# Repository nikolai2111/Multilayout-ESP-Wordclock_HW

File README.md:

# Multilayout-ESP-Wordclock_HW
This is the first unofficial hardware (PCB) for the [Multilayout-ESP-Wordclock](https://github.com/ESPWortuhr/Multilayout-ESP-Wordclock). The currently supported layout is a 10x11 with the 4 LEDs in the corner (total 114 LEDs). The dimensions are 240 x 240 mm. In the future, maybe more than one PCBs will be available as branch, but we will see how it goes.

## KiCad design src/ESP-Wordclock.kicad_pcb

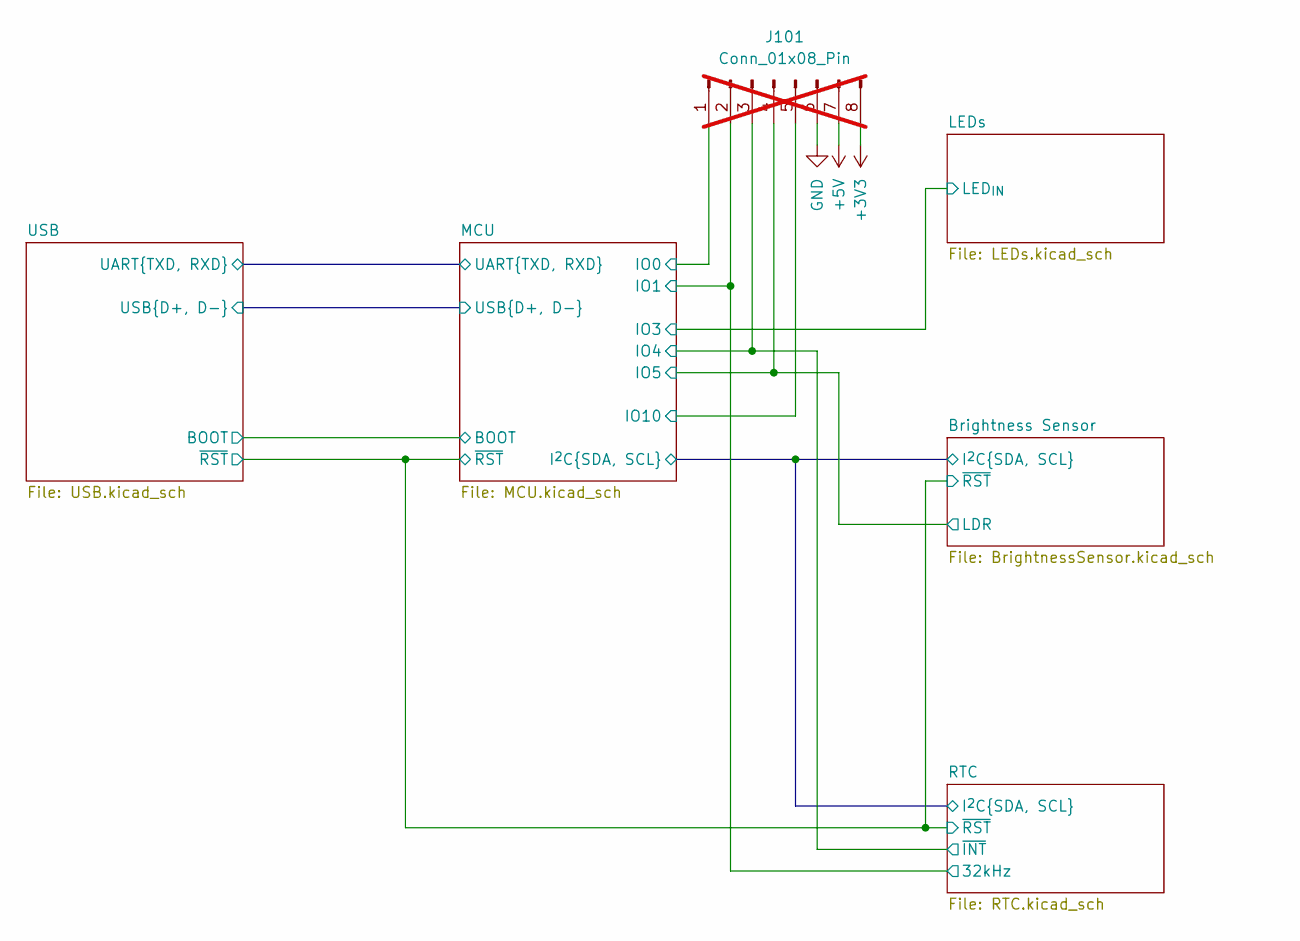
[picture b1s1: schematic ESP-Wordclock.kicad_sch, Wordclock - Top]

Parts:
J101: Conn_01x08_Pin; PinHeader_1x08_P2.54mm_Vertical; not fitted

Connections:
+3V3: J101.8; also elsewhere on the board
+5V: J101.7; also elsewhere on the board
/Brightness Sensor/LDR: J101.4; also elsewhere on the board
/MCU/IO0: J101.1; also elsewhere on the board
/MCU/IO1: J101.2; also elsewhere on the board
/MCU/IO4: J101.3; also elsewhere on the board
/MCU/IO10: J101.5; also elsewhere on the board
GND: J101.6; also elsewhere on the board

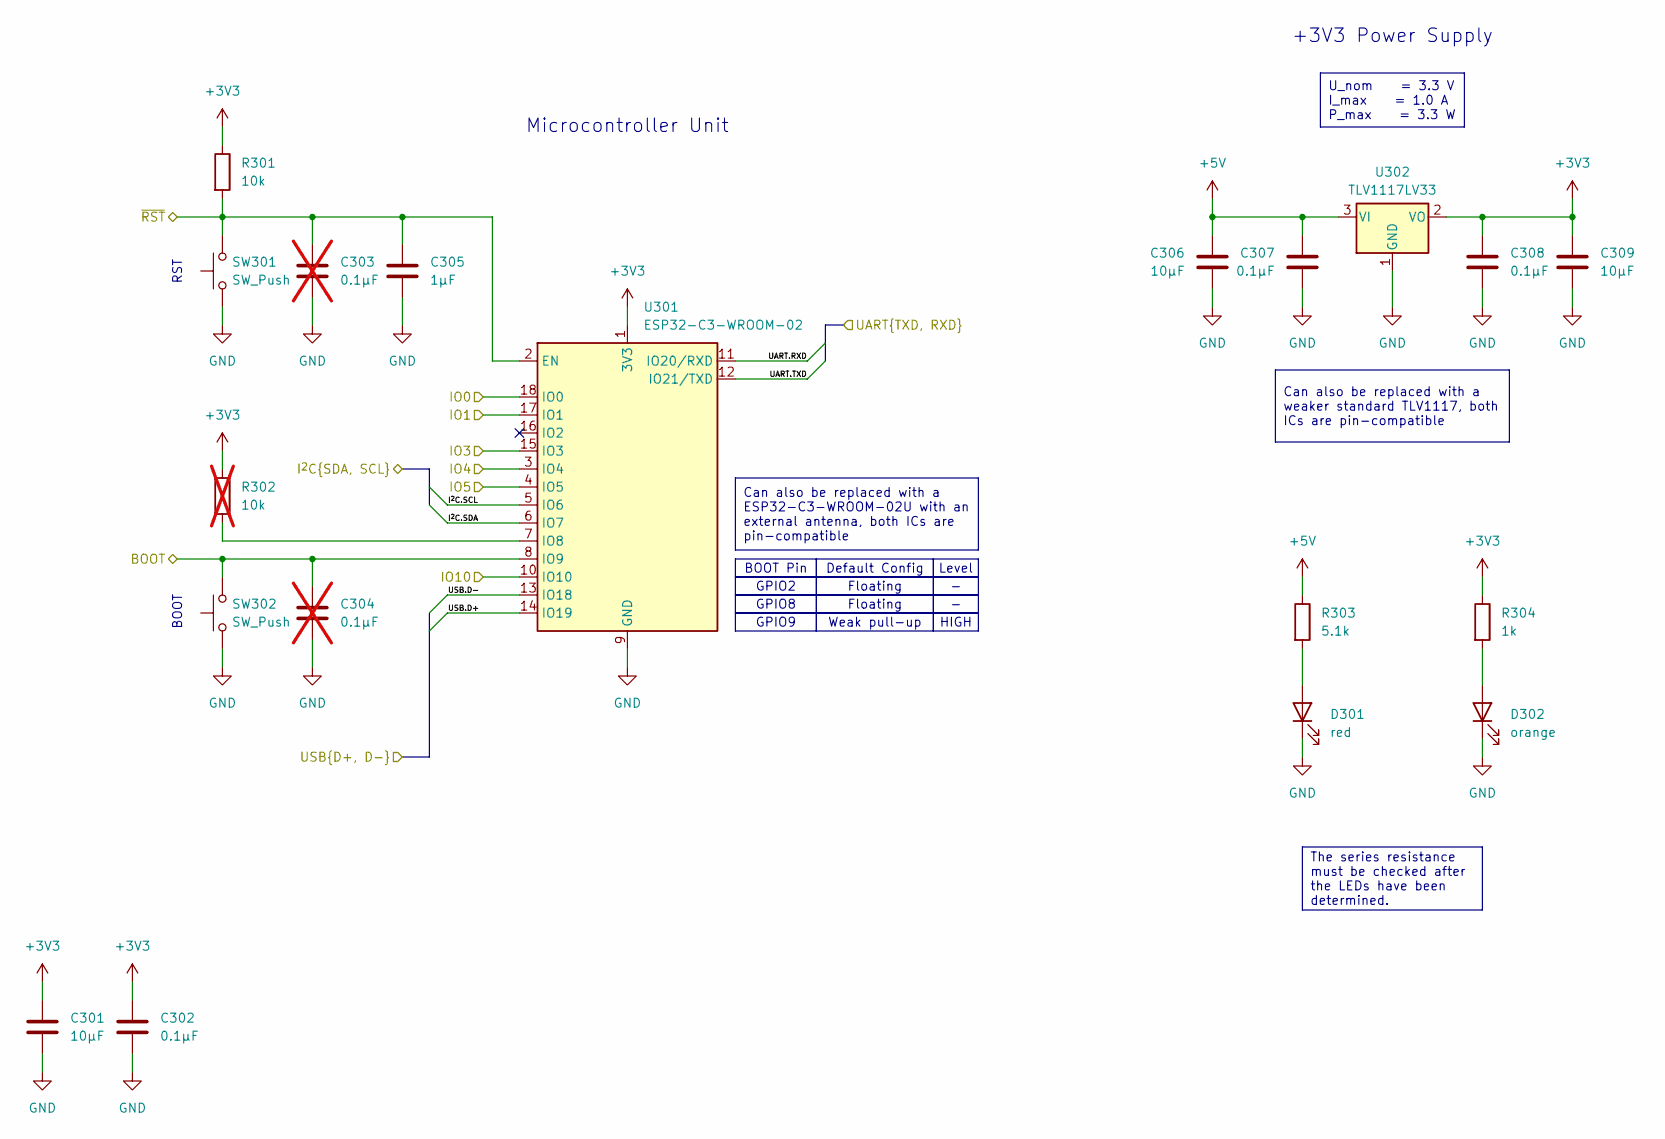
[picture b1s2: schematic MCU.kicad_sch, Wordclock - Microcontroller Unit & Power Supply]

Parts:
C301, C306, C309: 10µF; C_0805_2012Metric_Pad1.18x1.45mm_HandSolder; Manufacturer Part no. CL21A106KOQNNNE
C302, C307, C308: 0.1µF; C_0805_2012Metric_Pad1.18x1.45mm_HandSolder; Manufacturer Part no. CL21B104KCFNNNE
C303, C304: 0.1µF; C_0805_2012Metric_Pad1.18x1.45mm_HandSolder; Manufacturer Part no. CL21B104KCFNNNE; not fitted
C305: 1µF; C_0805_2012Metric_Pad1.18x1.45mm_HandSolder; Manufacturer Part no. CL21B105KPFNNNE
D301: red; LED_0805_2012Metric_Pad1.15x1.40mm_HandSolder; Manufacturer Part no. LTST-C171KRKT; LCSC C284871
D302: orange; LED_0805_2012Metric_Pad1.15x1.40mm_HandSolder; Manufacturer Part no. LTST-C170KFKT; LCSC C284931
R301: 10k; R_0805_2012Metric_Pad1.20x1.40mm_HandSolder; Manufacturer Part no. RC0805FR-0710KL
R302: 10k; R_0805_2012Metric_Pad1.20x1.40mm_HandSolder; Manufacturer Part no. RC0805FR-0710KL; not fitted
R303: 5.1k; R_0805_2012Metric_Pad1.20x1.40mm_HandSolder; Manufacturer Part no. RC0805FR-075K1L
R304: 1k; R_0805_2012Metric_Pad1.20x1.40mm_HandSolder; Manufacturer Part no. RC0805FR-071KL
SW301, SW302: SW_Push; SW_SPST_PTS810; Manufacturer Part no. PTS810 SJK 250 SMTR LFS; LCSC C221896
U301: ESP32-C3-WROOM-02; Manufacturer Part no. ESP32-C3-WROOM-02-N4; LCSC C2934560
U302: TLV1117LV33; SOT-223-3_TabPin2; Manufacturer Part no. TLV1117LV33DCYR; LCSC C15578

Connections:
+3V3: C301.1, C302.1, C308.1, C309.1, R301.1, R302.1, R304.1, U301.1 (3V3), U302.2 (VO); also elsewhere on the board
+5V: C306.1, C307.1, R303.1, U302.3 (VI); also elsewhere on the board
/Brightness Sensor/I^{2}C.SCL: U301.5 (IO6); also elsewhere on the board
/Brightness Sensor/I^{2}C.SDA: U301.6 (IO7); also elsewhere on the board
/Brightness Sensor/LDR: U301.4 (IO5); also elsewhere on the board
/Brightness Sensor/~RST: C303.1, C305.1, R301.2, SW301.2, U301.2 (EN); also elsewhere on the board
/LEDs/LED_{IN}: U301.15 (IO3); also elsewhere on the board
/MCU/BOOT: C304.1, SW302.2, U301.8 (IO9); also elsewhere on the board
/MCU/IO0: U301.18 (IO0); also elsewhere on the board
/MCU/IO1: U301.17 (IO1); also elsewhere on the board
/MCU/IO4: U301.3 (IO4); also elsewhere on the board
/MCU/IO10: U301.10 (IO10); also elsewhere on the board
/MCU/UART.RXD: U301.11 (IO20/RXD); also elsewhere on the board
/MCU/UART.TXD: U301.12 (IO21/TXD); also elsewhere on the board
/MCU/USB.D+: U301.14 (IO19); also elsewhere on the board
/MCU/USB.D-: U301.13 (IO18); also elsewhere on the board
GND: C301.2, C302.2, C303.2, C304.2, C305.2, C306.2, C307.2, C308.2, C309.2, D301.1 (K), D302.1 (K), SW301.1, SW302.1, U301.9 (GND), U301.19 (GND), U302.1 (GND); also elsewhere on the board
unnamed: D301.2 (A), R303.2
unnamed: D302.2 (A), R304.2
unnamed: R302.2, U301.7 (IO8)

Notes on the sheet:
Floating
BOOT Pin
GPIO8
Can also be replaced with a ESP32-C3-WROOM-02U with an external antenna, both ICs are pin-compatible
U_nom = 3.3 V I_max = 1.0 A P_max = 3.3 W
Default Config
Level
GPIO9
Weak pull-up
The series resistance must be checked after the LEDs have been determined.
HIGH
Can also be replaced with a weaker standard TLV1117, both ICs are pin-compatible
GPIO2
+3V3 Power Supply
Microcontroller Unit
RST
BOOT

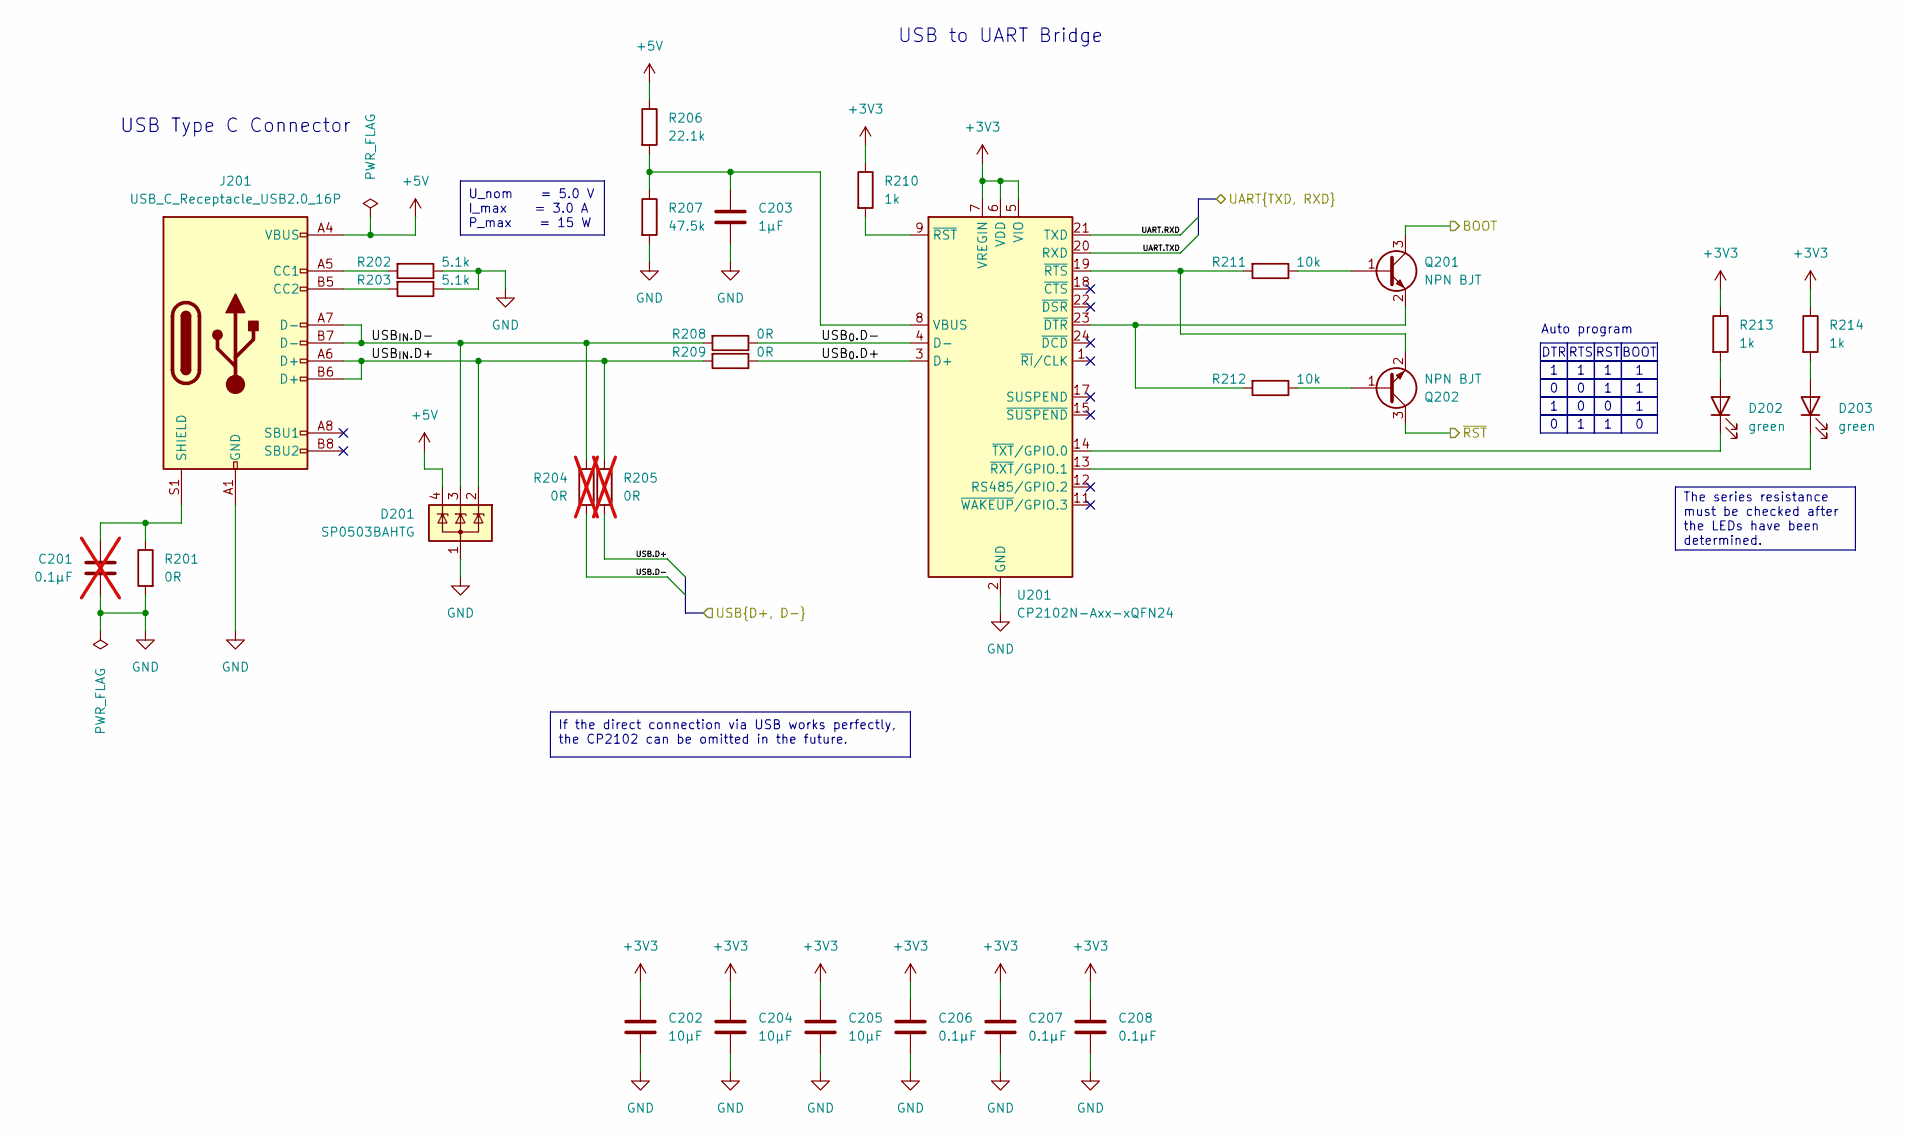
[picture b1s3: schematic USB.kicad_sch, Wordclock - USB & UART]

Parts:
C201: 0.1µF; C_0805_2012Metric_Pad1.18x1.45mm_HandSolder; Manufacturer Part no. CL21B104KCFNNNE; not fitted
C202, C204, C205: 10µF; C_0805_2012Metric_Pad1.18x1.45mm_HandSolder; Manufacturer Part no. CL21A106KOQNNNE
C203: 1µF; C_0805_2012Metric_Pad1.18x1.45mm_HandSolder; Manufacturer Part no. CL21B105KPFNNNE
C206, C207, C208: 0.1µF; C_0805_2012Metric_Pad1.18x1.45mm_HandSolder; Manufacturer Part no. CL21B104KCFNNNE
D201: SP0503BAHTG; SOT-143_Handsoldering; Manufacturer Part no. SP0503BAHTG; LCSC C7074
D202, D203: green; LED_0805_2012Metric_Pad1.15x1.40mm_HandSolder; Manufacturer Part no. LTST-C171GKT; LCSC C913075
J201: USB_C_Receptacle_USB2.0_16P; USB_C_Receptacle_GCT_USB4105-xx-A_16P_TopMnt_Horizontal; Manufacturer Part no. USB4105-GF-A; LCSC C3020560
Q201, Q202: NPN BJT; SOT-23_Handsoldering; LCSC C49581
R201, R208, R209: 0R; R_0805_2012Metric_Pad1.20x1.40mm_HandSolder; Manufacturer Part no. RC0805JR-070RL
R202, R203: 5.1k; R_0805_2012Metric_Pad1.20x1.40mm_HandSolder; Manufacturer Part no. RC0805FR-075K1L
R204, R205: 0R; R_0805_2012Metric_Pad1.20x1.40mm_HandSolder; Manufacturer Part no. RC0805JR-070RL; not fitted
R206: 22.1k; R_0805_2012Metric_Pad1.20x1.40mm_HandSolder; Manufacturer Part no. RC0805FR-0722K1L; LCSC C17552
R207: 47.5k; R_0805_2012Metric_Pad1.20x1.40mm_HandSolder; Manufacturer Part no. RC0805FR-0747K5L; LCSC C26011
R210, R213, R214: 1k; R_0805_2012Metric_Pad1.20x1.40mm_HandSolder; Manufacturer Part no. RC0805FR-071KL
R211, R212: 10k; R_0805_2012Metric_Pad1.20x1.40mm_HandSolder; Manufacturer Part no. RC0805FR-0710KL
U201: CP2102N-Axx-xQFN24; QFN-24-1EP_4x4mm_P0.5mm_EP2.6x2.6mm_ThermalVias; Manufacturer Part no. CP2102N-A02-GQFN24R; LCSC C969151

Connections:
+3V3: C202.1, C204.1, C205.1, C206.1, C207.1, C208.1, R210.1, R213.1, R214.1, U201.5 (VIO), U201.6 (VDD), U201.7 (VREGIN); also elsewhere on the board
+5V: D201.4 (K), J201.A4 (VBUS), J201.A9 (VBUS), J201.B4 (VBUS), J201.B9 (VBUS), R206.1; also elsewhere on the board
/Brightness Sensor/~RST: Q202.3 (C); also elsewhere on the board
/MCU/BOOT: Q201.3 (C); also elsewhere on the board
/MCU/UART.RXD: U201.21 (TXD); also elsewhere on the board
/MCU/UART.TXD: U201.20 (RXD); also elsewhere on the board
/MCU/USB.D+: R205.2; also elsewhere on the board
/MCU/USB.D-: R204.2; also elsewhere on the board
/USB/USB_{0}.D+: R209.1, U201.3 (D+)
/USB/USB_{0}.D-: R208.1, U201.4 (D-)
/USB/USB_{IN}.D+: D201.2 (K), J201.A6 (D+), J201.B6 (D+), R205.1, R209.2
/USB/USB_{IN}.D-: D201.3 (K), J201.A7 (D-), J201.B7 (D-), R204.1, R208.2
GND: C201.2, C202.2, C203.2, C204.2, C205.2, C206.2, C207.2, C208.2, D201.1 (A), J201.A1 (GND), J201.A12 (GND), J201.B1 (GND), J201.B12 (GND), R201.2, R202.1, R203.1, R207.2, U201.2 (GND), U201.25 (GND); also elsewhere on the board
unnamed: D202.2 (A), R213.2
unnamed: D202.1 (K), U201.14 (~TXT/GPIO.0)
unnamed: D203.2 (A), R214.2
unnamed: D203.1 (K), U201.13 (~RXT/GPIO.1)
unnamed: J201.A5 (CC1), R202.2
unnamed: J201.B5 (CC2), R203.2
unnamed: C201.1, J201.S1 (SHIELD), R201.1
unnamed: Q201.1 (B), R211.1
unnamed: Q201.2 (E), R212.2, U201.23 (~DTR)
unnamed: Q202.1 (B), R212.1
unnamed: Q202.2 (E), R211.2, U201.19 (~RTS)
unnamed: C203.1, R206.2, R207.1, U201.8 (VBUS)
unnamed: R210.2, U201.9 (~RST)

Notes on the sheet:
The series resistance must be checked after the LEDs have been determined.
DTR
RST
RTS
U_nom = 5.0 V I_max = 3.0 A P_max = 15 W
BOOT
If the direct connection via USB works perfectly, the CP2102 can be omitted in the future.
USB Type C Connector
Auto program
USB to UART Bridge

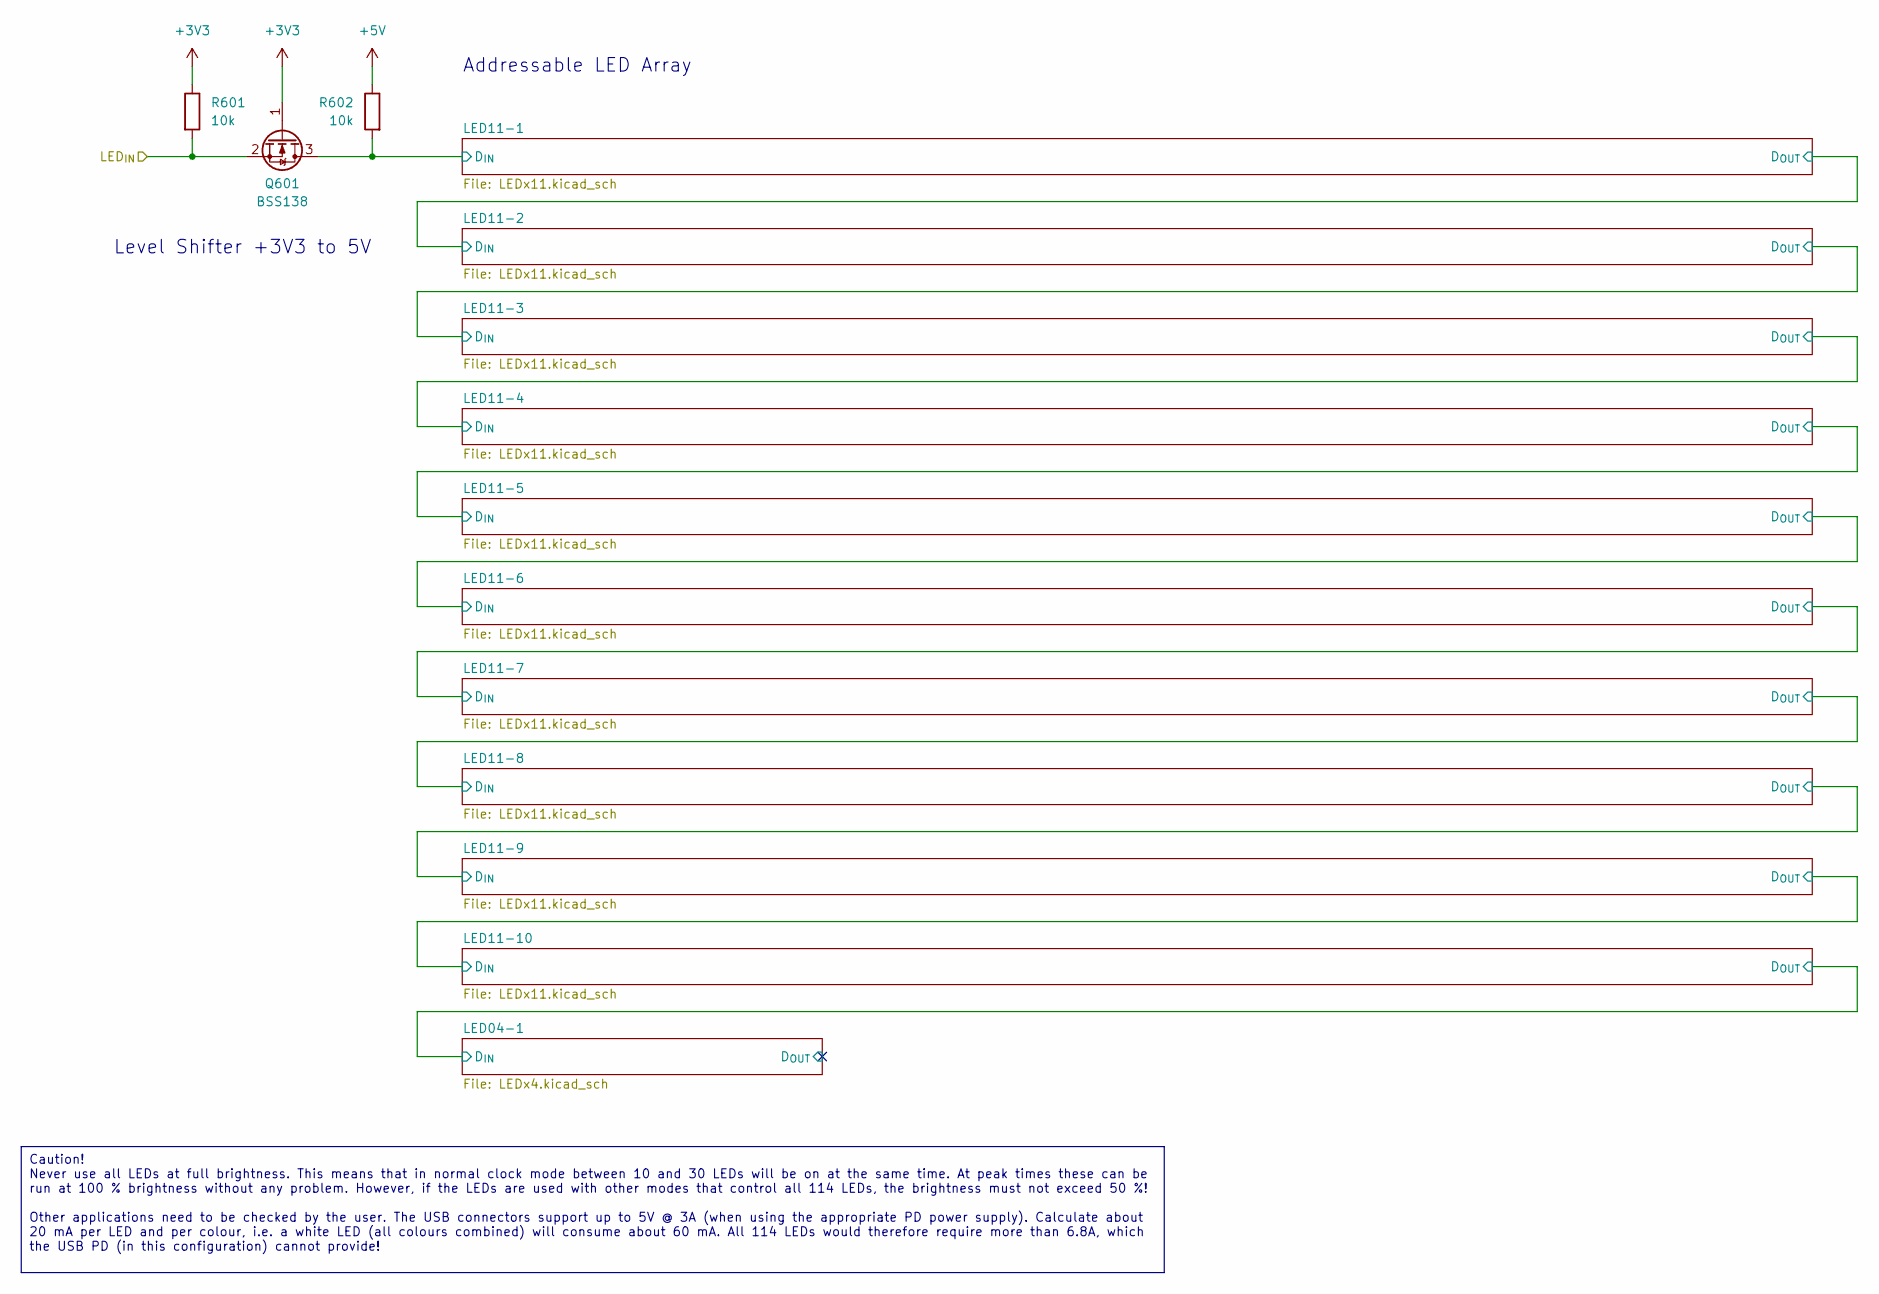
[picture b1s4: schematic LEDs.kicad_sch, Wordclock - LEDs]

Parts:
Q601: BSS138; SOT-23_Handsoldering; Manufacturer Part no. BSS138; LCSC C518792
R601, R602: 10k; R_0805_2012Metric_Pad1.20x1.40mm_HandSolder; Manufacturer Part no. RC0805FR-0710KL

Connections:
+3V3: Q601.1 (G), R601.1; also elsewhere on the board
+5V: R602.1; also elsewhere on the board
/LEDs/LED11-1/D_{IN}: Q601.3 (D), R602.2; also elsewhere on the board
/LEDs/LED_{IN}: Q601.2 (S), R601.2; also elsewhere on the board

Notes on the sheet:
Caution! Never use all LEDs at full brightness. This means that in normal clock mode between 10 and 30 LEDs will be on at the same time. At peak times these can be run at 100 % brightness without any problem. However, if the LEDs are used with other modes that control all 114 LEDs, the brightness m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
Level Shifter +3V3 to 5V
Addressable LED Array

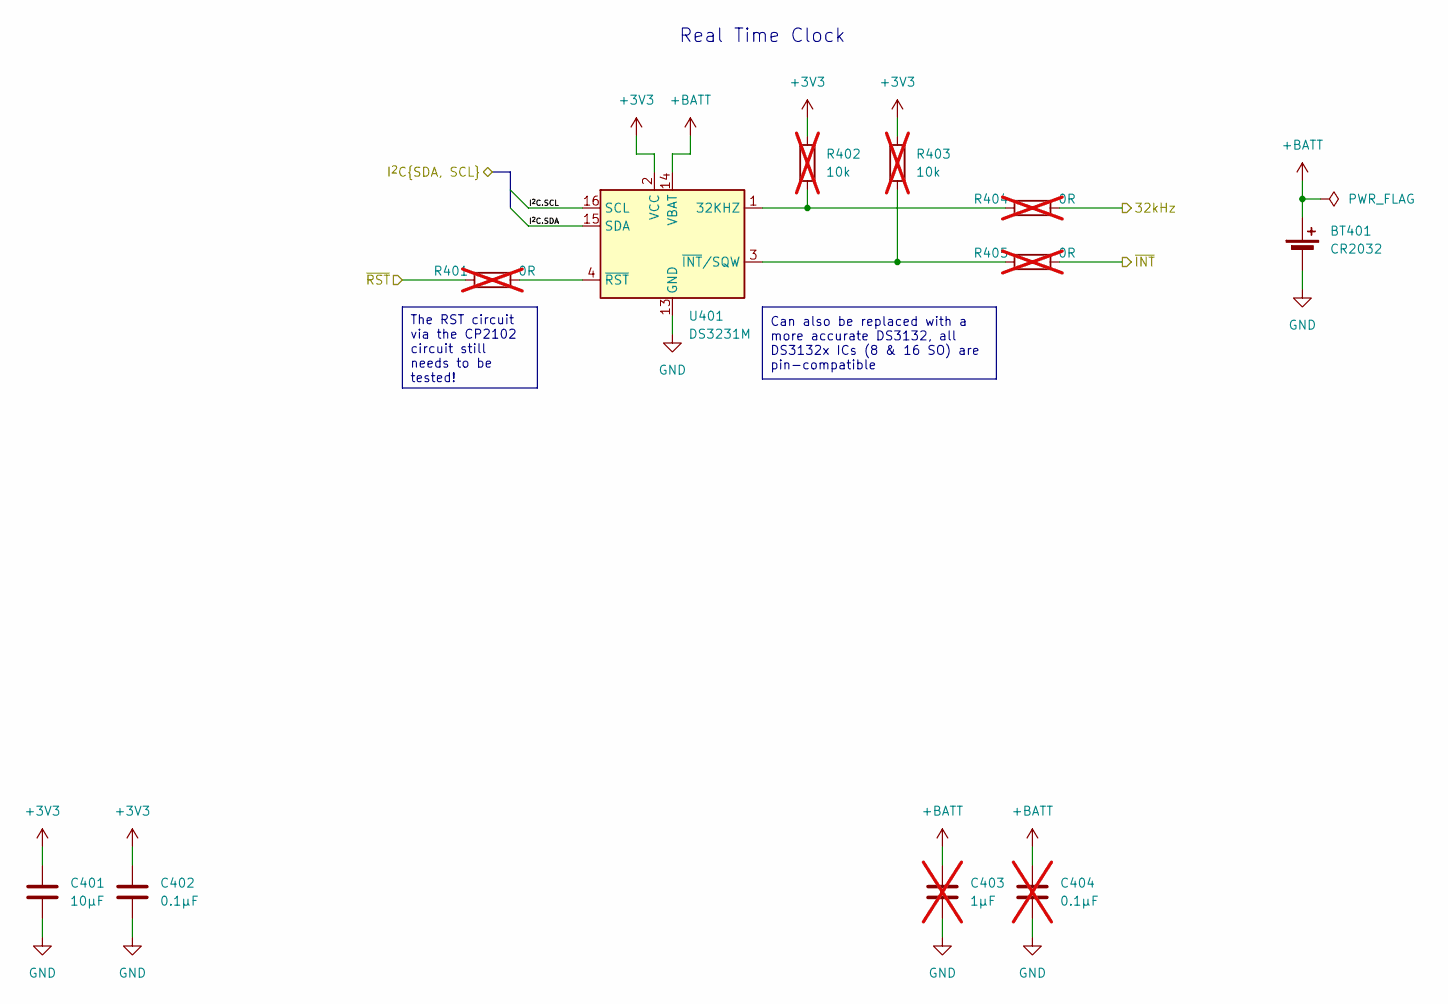
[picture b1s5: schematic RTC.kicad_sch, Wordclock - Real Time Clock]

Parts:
BT401: CR2032; BatteryHolder_Keystone_3002_1x2032; Manufacturer Part no. 2898; LCSC C6379018
C401: 10µF; C_0805_2012Metric_Pad1.18x1.45mm_HandSolder; Manufacturer Part no. CL21A106KOQNNNE
C402: 0.1µF; C_0805_2012Metric_Pad1.18x1.45mm_HandSolder; Manufacturer Part no. CL21B104KCFNNNE
C403: 1µF; C_0805_2012Metric_Pad1.18x1.45mm_HandSolder; Manufacturer Part no. CL21B105KPFNNNE; not fitted
C404: 0.1µF; C_0805_2012Metric_Pad1.18x1.45mm_HandSolder; Manufacturer Part no. CL21B104KCFNNNE; not fitted
R401, R404, R405: 0R; R_0805_2012Metric_Pad1.20x1.40mm_HandSolder; Manufacturer Part no. RC0805JR-070RL; not fitted
R402, R403: 10k; R_0805_2012Metric_Pad1.20x1.40mm_HandSolder; Manufacturer Part no. RC0805FR-0710KL; not fitted
U401: DS3231M; SOIC-16W_7.5x10.3mm_P1.27mm; Manufacturer Part no. DS3231M+TRL; LCSC C107410

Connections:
+3V3: C401.1, C402.1, R402.1, R403.1, U401.2 (VCC); also elsewhere on the board
+BATT: BT401.1 (+), C403.1, C404.1, U401.14 (VBAT)
/Brightness Sensor/I^{2}C.SCL: U401.16 (SCL); also elsewhere on the board
/Brightness Sensor/I^{2}C.SDA: U401.15 (SDA); also elsewhere on the board
/Brightness Sensor/~RST: R401.2; also elsewhere on the board
/MCU/IO1: R404.1; also elsewhere on the board
/MCU/IO4: R405.1; also elsewhere on the board
GND: BT401.2 (-), C401.2, C402.2, C403.2, C404.2, U401.5 (GND), U401.6 (GND), U401.7 (GND), U401.8 (GND), U401.9 (GND), U401.10 (GND), U401.11 (GND), U401.12 (GND), U401.13 (GND); also elsewhere on the board
unnamed: R402.2, R404.2, U401.1 (32KHZ)
unnamed: R403.2, R405.2, U401.3 (~INT/SQW)
unnamed: R401.1, U401.4 (~RST)

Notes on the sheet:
Can also be replaced with a more accurate DS3132, all DS3132x ICs (8 & 16 SO) are pin-compatible
The RST circuit via the CP2102 circuit still needs to be tested!
Real Time Clock

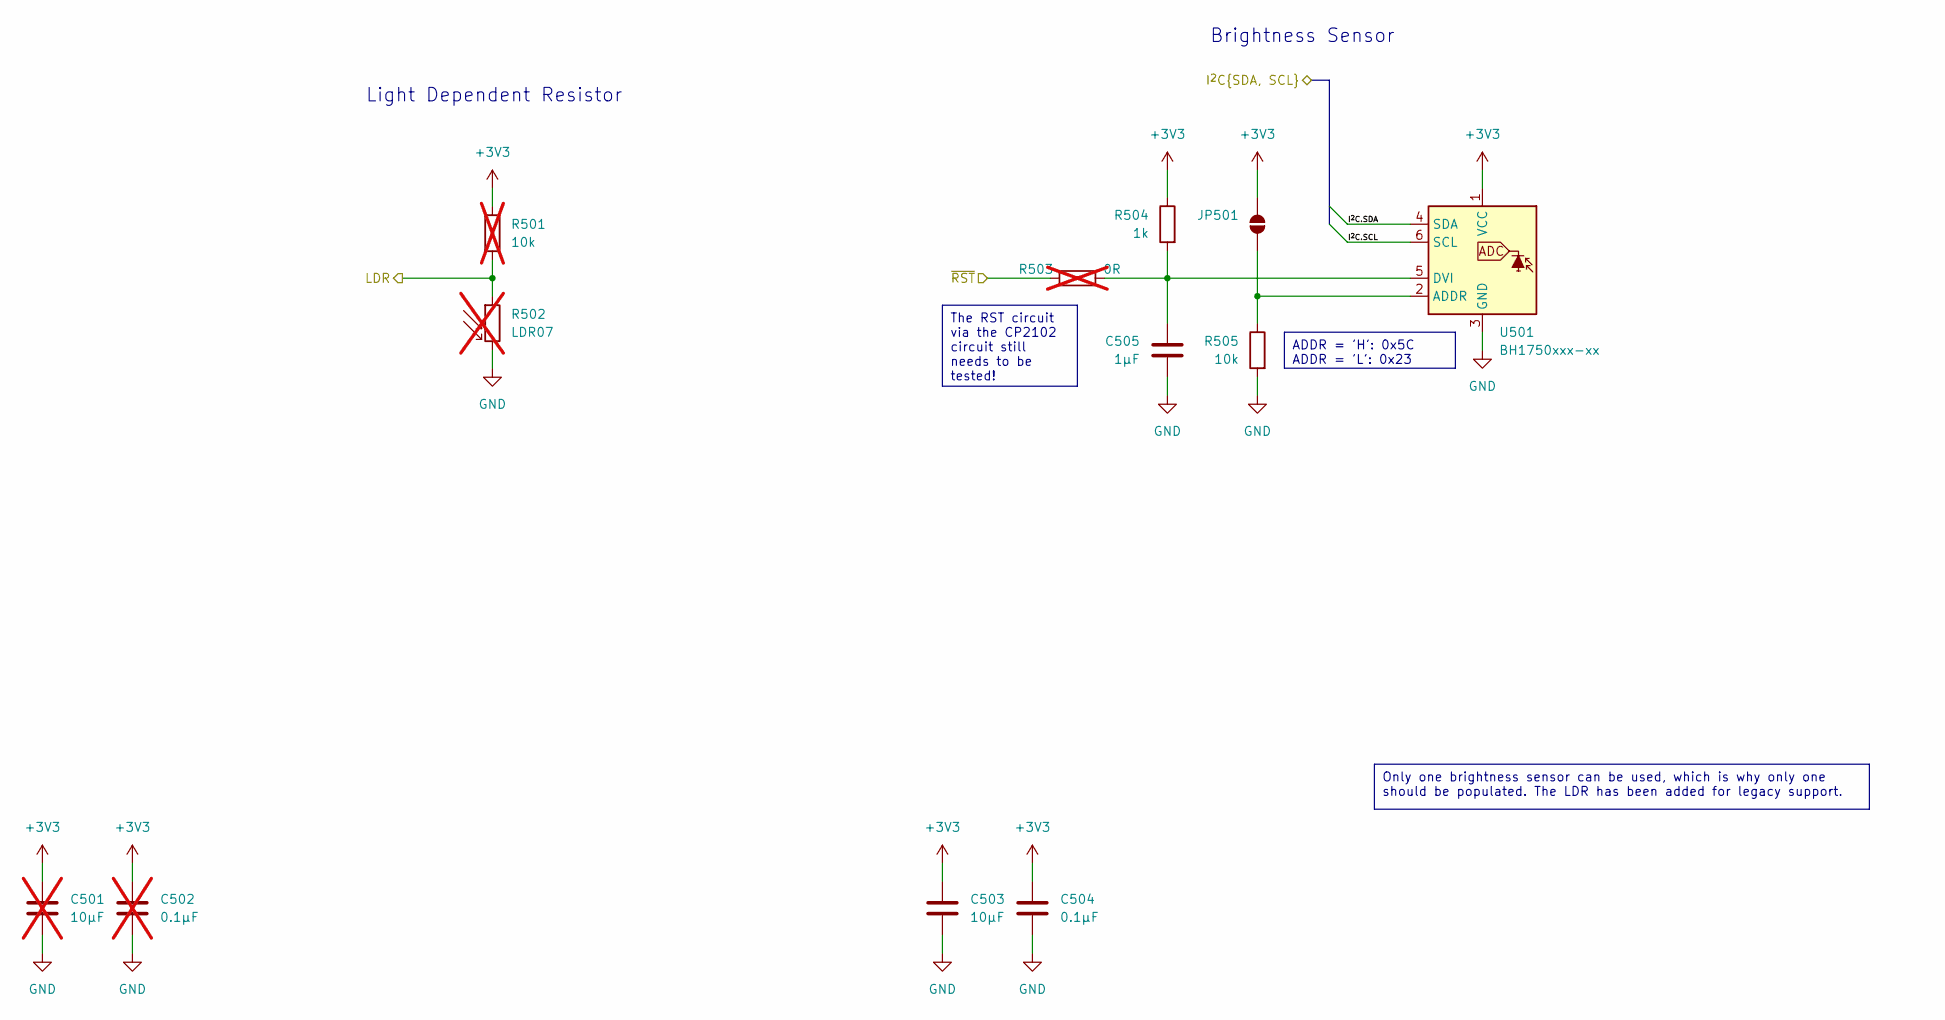
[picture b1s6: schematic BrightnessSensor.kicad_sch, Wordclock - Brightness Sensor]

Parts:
C501: 10µF; C_0805_2012Metric_Pad1.18x1.45mm_HandSolder; Manufacturer Part no. CL21A106KOQNNNE; not fitted
C502: 0.1µF; C_0805_2012Metric_Pad1.18x1.45mm_HandSolder; Manufacturer Part no. CL21B104KCFNNNE; not fitted
C503: 10µF; C_0805_2012Metric_Pad1.18x1.45mm_HandSolder; Manufacturer Part no. CL21A106KOQNNNE
C504: 0.1µF; C_0805_2012Metric_Pad1.18x1.45mm_HandSolder; Manufacturer Part no. CL21B104KCFNNNE
C505: 1µF; C_0805_2012Metric_Pad1.18x1.45mm_HandSolder; Manufacturer Part no. CL21B105KPFNNNE
JP501: SolderJumper_2_Open; SolderJumper-2_P1.3mm_Open_RoundedPad1.0x1.5mm
R501: 10k; R_0805_2012Metric_Pad1.20x1.40mm_HandSolder; Manufacturer Part no. RC0805FR-0710KL; not fitted
R502: LDR07; R_LDR_5.1x4.3mm_P3.4mm_Vertical; not fitted
R503: 0R; R_0805_2012Metric_Pad1.20x1.40mm_HandSolder; Manufacturer Part no. RC0805JR-070RL; not fitted
R504: 1k; R_0805_2012Metric_Pad1.20x1.40mm_HandSolder; Manufacturer Part no. RC0805FR-071KL
R505: 10k; R_0805_2012Metric_Pad1.20x1.40mm_HandSolder; Manufacturer Part no. RC0805FR-0710KL
U501: BH1750xxx-xx; HVSOF6; Manufacturer Part no. BH1750FVI-TR; LCSC C78960

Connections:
+3V3: C501.1, C502.1, C503.1, C504.1, JP501.2 (B), R501.1, R504.1, U501.1 (VCC); also elsewhere on the board
/Brightness Sensor/I^{2}C.SCL: U501.6 (SCL); also elsewhere on the board
/Brightness Sensor/I^{2}C.SDA: U501.4 (SDA); also elsewhere on the board
/Brightness Sensor/LDR: R501.2, R502.1; also elsewhere on the board
/Brightness Sensor/~RST: R503.2; also elsewhere on the board
GND: C501.2, C502.2, C503.2, C504.2, C505.2, R502.2, R505.2, U501.3 (GND); also elsewhere on the board
unnamed: JP501.1 (A), R505.1, U501.2 (ADDR)
unnamed: C505.1, R503.1, R504.2, U501.5 (DVI)

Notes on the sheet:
Only one brightness sensor can be used, which is why only one should be populated. The LDR has been added for legacy support.
The RST circuit via the CP2102 circuit still needs to be tested!
ADDR = 'H': 0x5C ADDR = 'L': 0x23
Brightness Sensor
Light Dependent Resistor

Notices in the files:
src/BrightnessSensor.kicad_sch:
CERN-OHL-P
